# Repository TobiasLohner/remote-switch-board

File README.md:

# Remote Switch Board

This hardware project aims to provide a small form factor board for smart home projects.

The primary goal is to have a platform for remotely switching a garden watering system. The board can be partially populated if fewer switching outputs or other features are not required.

The board was made with KiCad 6.0.

## Main Features

* 8 solid state switches with current measurement
* SX1231 RF chip (compatible to RFM69, 433 / 868 / 915 MHz ISM frequency bands)
* STM32L0 microcontroller (optional)
* Raspberry PI header (optional)
* Frequency counter input
* Thermistor input
* Operating voltage: 12 V DC

## Microcontroller

The board has the option to either use an STM32L0 microcontroller or a Raspberry Pi to control the RF module and the switches. The microcontroller uses SPI to:
* control the switches via a shift register
* read the current feedback from a MCP3008
* communicate with the SX1231 RF chip

Further digital/analog inputs are used for:
* Thermistor input (analog input)
* Frequency counter (digital input)

Both SPI and digital input is also wired to the Raspberry PI header, such that a Raspberry Pi could be used instead of the microcontroller.

## SX1231
The SX1231 is a RF tranciever capable to be operated at license-free 433 / 868 / 915 MHz frequency bands. Tested range using 868 MHz was more than 500 meter in line-of-sight, sufficient for smart home applications.

## Electrical Characteristics
* Main operating voltage: 12 V
* Includes 5 V output to supply a Raspberry PI
* Total current limit approx. 5 A (might be more, untested)
* Switches: 12 V / 2.5 A each

# Licence
Shield: [![CC BY-SA 4.0][cc-by-sa-shield]][cc-by-sa]

This work is licensed under a
[Creative Commons Attribution-ShareAlike 4.0 International License][cc-by-sa].

[![CC BY-SA 4.0][cc-by-sa-image]][cc-by-sa]

[cc-by-sa]: http://creativecommons.org/licenses/by-sa/4.0/
[cc-by-sa-image]: https://licensebuttons.net/l/by-sa/4.0/88x31.png
[cc-by-sa-shield]: https://img.shields.io/badge/License-CC%20BY--SA%204.0-lightgrey.svg

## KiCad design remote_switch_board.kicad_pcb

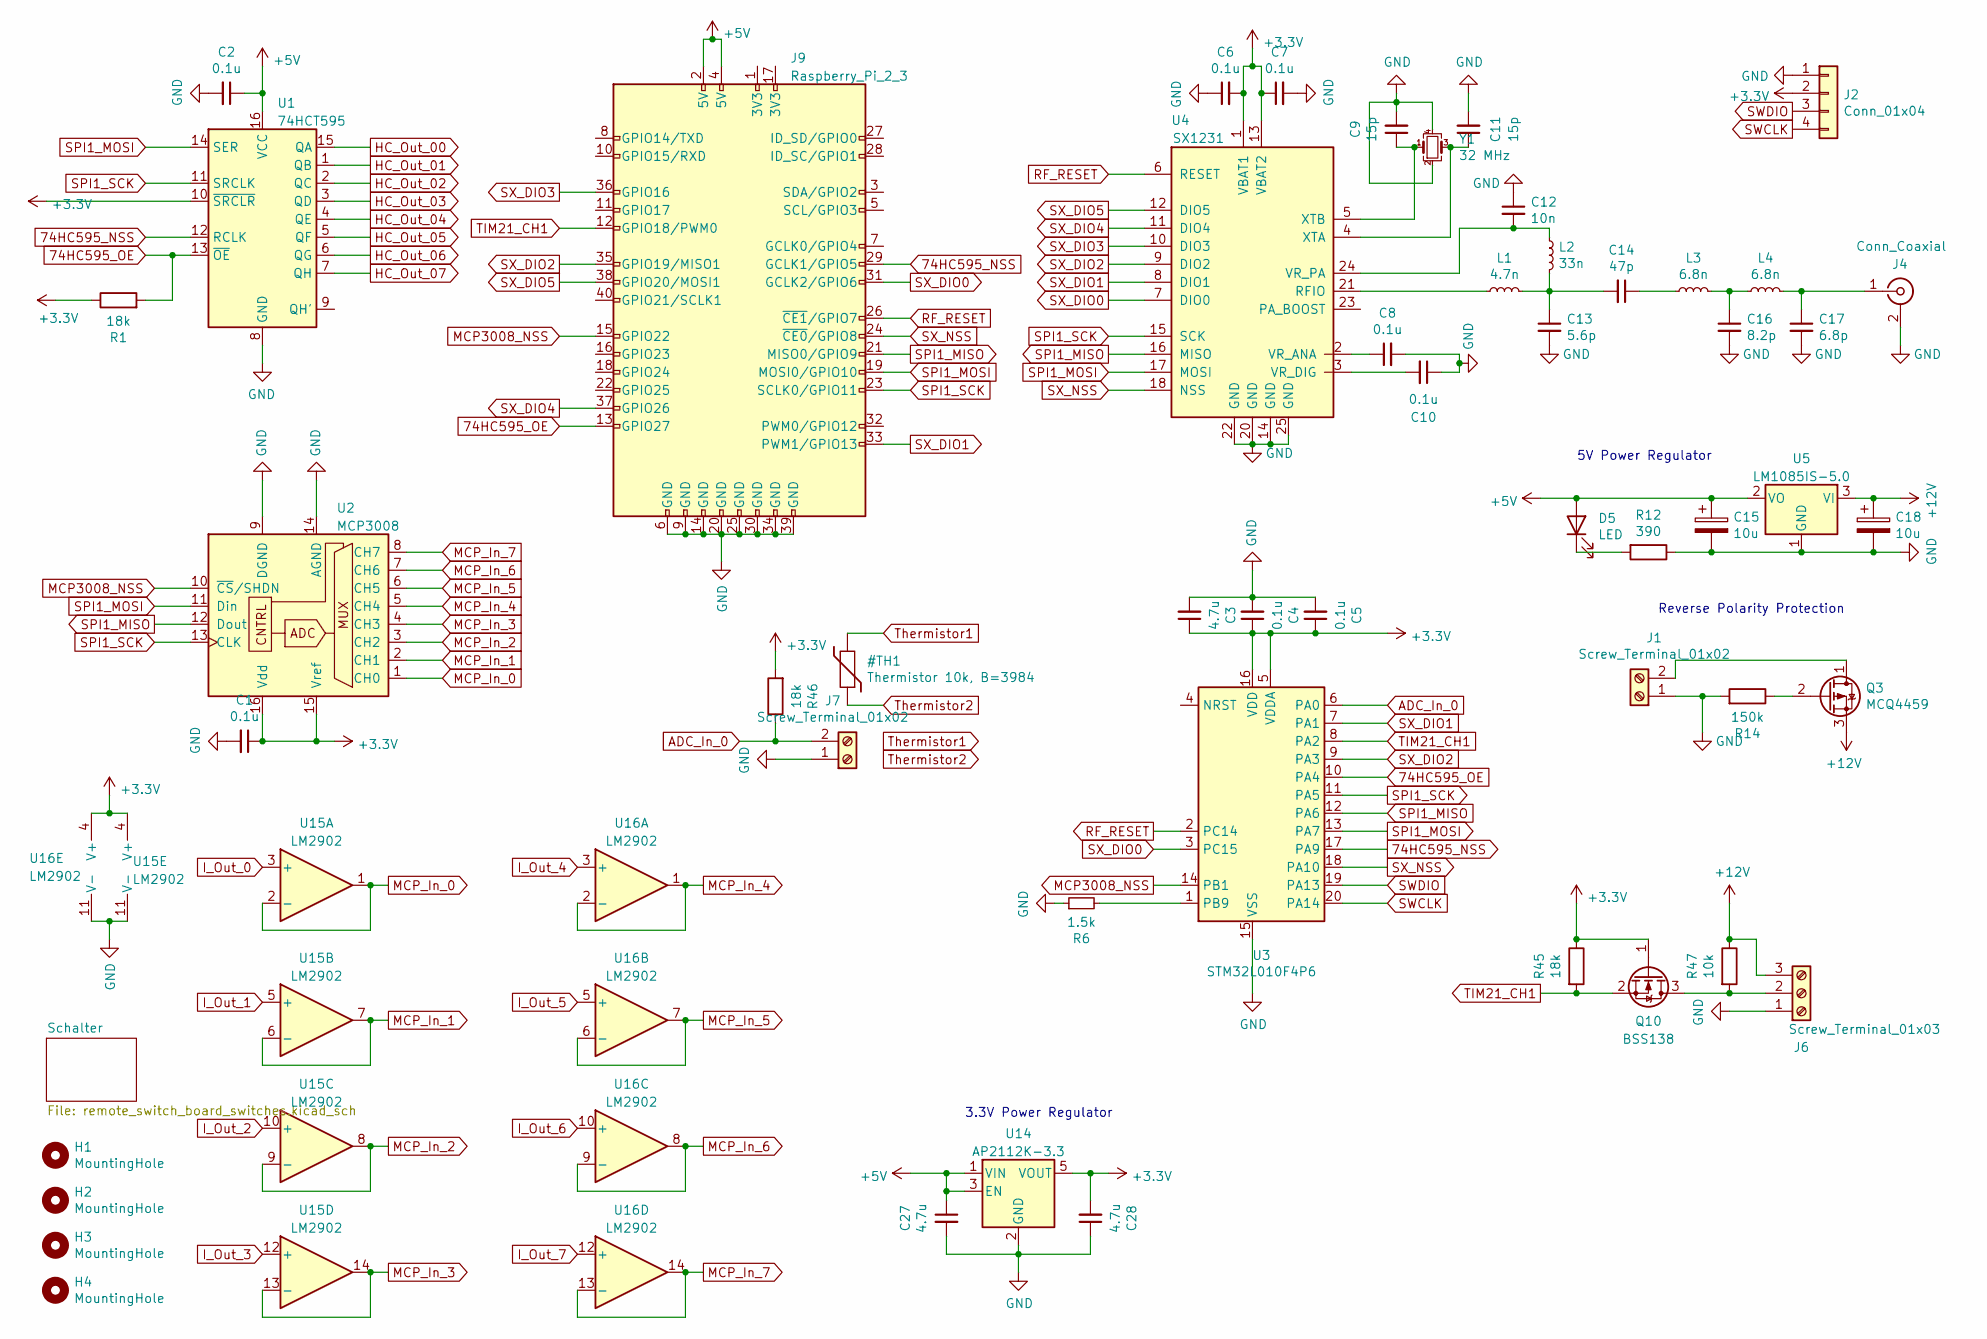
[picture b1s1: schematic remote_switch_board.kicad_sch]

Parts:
C1, C2, C4, C5, C6, C7, C8, C10: 0.1u; C_0603_1608Metric; Mouser-Nr. 581-0603YC104MAT4A
C3, C27, C28: 4.7u; C_0603_1608Metric; Mouser-Nr. 187-CL10B475KQ8NQNC
C9, C11: 15p; C_0603_1608Metric; Mouser-Nr. 80-C0603C150J5G
C12: 10n; C_0603_1608Metric; Mouser-Nr. 581-06035C103MAT4A
C13: 5.6p; C_0603_1608Metric; Mouser-Nr. 581-06035A5R6J
C14: 47p; C_0603_1608Metric; Mouser-Nr. 80-C0603C470J1G
C15, C18: 10u; CP_EIA-7343-31_Kemet-D; Mouser-Nr. 74-TR3D106K035C0400
C16: 8.2p; C_0603_1608Metric; Mouser-Nr. 80-C0603C829J5G
C17: 6.8p; C_0603_1608Metric; Mouser-Nr. 80-C0603C689J5G
D5: LED; LED_0805_2012Metric
H1, H2, H3, H4: MountingHole; MountingHole_2.7mm_Pad
J1, J7: Screw_Terminal_01x02; TerminalBlock_Phoenix_PT-1,5-2-3.5-H_1x02_P3.50mm_Horizontal; Mouser-Nr. 651-1984617
J2: Conn_01x04; PinHeader_1x04_P2.54mm_Vertical
J4: Conn_Coaxial; U.FL_Hirose_U.FL-R-SMT-1_Vertical; Mouser-Nr. 798-U.FL-R-SMT-110
J6: Screw_Terminal_01x03; TerminalBlock_Phoenix_PT-1,5-3-3.5-H_1x03_P3.50mm_Horizontal; Mouser-Nr. 651-1984620
J9: Raspberry_Pi_2_3; PinHeader_2x20_P2.54mm_Vertical
L1: 4.7n; L_0603_1608Metric; Mouser-Nr. 81-LQW18AN4N7C80D
L2: 33n; L_0603_1608Metric; Mouser-Nr. 81-LQW18AN33NJ00D
L3, L4: 6.8n; L_0603_1608Metric; Mouser-Nr. 81-LQW18AN6N8C00D
Q3: MCQ4459; MCQ4459_SOP-8_5.28x5.23mm_P1.27mm; Mouser-Nr. 833-MCQ4459-TP
Q10: BSS138; SOT-23; Mouser-Nr. 771-BSS138P215
R1, R45, R46: 18k; R_0603_1608Metric; Mouser-Nr. 603-RC0603FR-1018KL
R6: 1.5k; R_0603_1608Metric; Mouser-Nr. 652-CR0603FX-1501ELF
R12: 390; R_0603_1608Metric; Mouser-Nr. 603-RC0603FR-07390RL
R14: 150k; R_0603_1608Metric; Mouser-Nr. 603-RC0603FR-07150KL
R47: 10k; R_0603_1608Metric; Mouser-Nr. 603-RC0603FR-1010KL
U1: 74HCT595; TSSOP-16_4.4x5mm_P0.65mm; Mouser-Nr. 74HCT595PW,118
U2: MCP3008; SOIC-16_3.9x9.9mm_P1.27mm; Mouser-Nr. 579-MCP3008T-I/SL
U3: STM32L010F4P6; TSSOP-20_4.4x6.5mm_P0.65mm; Mouser-Nr. 511-STM32L010F4P6
U4: SX1231; QFN-24-1EP_5x5mm_P0.65mm_EP3.4x3.4mm; Mouser-Nr. 947-SX1231IMLTRT
U5: LM1085IS-5.0; TO-263-3_TabPin2; Mouser-Nr. 926-LM1085IS50NOPB
U14: AP2112K-3.3; SOT-23-5
U15, U16: LM2902; TSSOP-14_4.4x5mm_P0.65mm
Y1: 32 MHz; Crystal_SMD_2520-4Pin_2.5x2.0mm; Mouser-Nr. 344-NX2520SA32MCSW2

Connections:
74HC595_NSS: J9.29 (GCLK1/GPIO5), U1.12 (RCLK), U3.17 (PA9)
74HC595_OE: J9.13 (GPIO27), R1.2, U1.13 (~OE), U3.10 (PA4)
+3.3V: C1.1, C3.1, C4.1, C5.1, C6.2, C7.1, C28.2, J2.2, Q10.1 (G), R1.1, R45.1, R46.2, U1.10 (~SRCLR), U2.15 (Vref), U2.16 (Vdd), U3.5 (VDDA), U3.16 (VDD), U4.1 (VBAT1), U4.13 (VBAT2), U14.5 (VOUT), U15.4 (V+), U16.4 (V+); also elsewhere on the board
+5V: C2.1, C15.1, C27.1, D5.2 (A), J9.2 (5V), J9.4 (5V), U1.16 (VCC), U5.2 (VO), U14.1 (VIN), U14.3 (EN)
+12V: C18.1, J6.3, Q3.3 (S), R47.1, U5.3 (VI); also elsewhere on the board
ADC_In_0: J7.2, R46.1, U3.6 (PA0)
GND: C1.2, C2.2, C3.2, C4.2, C5.2, C6.1, C7.2, C8.2, C9.2, C10.1, C11.2, C12.1, C13.2, C15.2, C16.2, C17.2, C18.2, C27.2, C28.1, J1.1, J2.1, J4.2 (Ext), J6.1, J7.1, J9.6 (GND), J9.9 (GND), J9.14 (GND), J9.20 (GND), J9.25 (GND), J9.30 (GND), J9.34 (GND), J9.39 (GND), R6.1, R12.1, R14.2, U1.8 (GND), U2.9 (DGND), U2.14 (AGND), U3.15 (VSS), U4.14 (GND), U4.20 (GND), U4.22 (GND), U4.25 (GND), U5.1 (GND), U14.2 (GND), U15.11 (V-), U16.11 (V-), Y1.2, Y1.4; also elsewhere on the board
HC_Out_00: U1.15 (QA); also elsewhere on the board
HC_Out_01: U1.1 (QB); also elsewhere on the board
HC_Out_02: U1.2 (QC); also elsewhere on the board
HC_Out_03: U1.3 (QD); also elsewhere on the board
HC_Out_04: U1.4 (QE); also elsewhere on the board
HC_Out_05: U1.5 (QF); also elsewhere on the board
HC_Out_06: U1.6 (QG); also elsewhere on the board
HC_Out_07: U1.7 (QH); also elsewhere on the board
I_Out_0: U15.3 (+); also elsewhere on the board
I_Out_1: U15.5 (+); also elsewhere on the board
I_Out_2: U15.10 (+); also elsewhere on the board
I_Out_3: U15.12 (+); also elsewhere on the board
I_Out_4: U16.3 (+); also elsewhere on the board
I_Out_5: U16.5 (+); also elsewhere on the board
I_Out_6: U16.10 (+); also elsewhere on the board
I_Out_7: U16.12 (+); also elsewhere on the board
MCP3008_NSS: J9.15 (GPIO22), U2.10 (~CS/SHDN), U3.14 (PB1)
MCP_In_0: U2.1 (CH0), U15.1, U15.2 (-)
MCP_In_1: U2.2 (CH1), U15.6 (-), U15.7
MCP_In_2: U2.3 (CH2), U15.8, U15.9 (-)
MCP_In_3: U2.4 (CH3), U15.13 (-), U15.14
MCP_In_4: U2.5 (CH4), U16.1, U16.2 (-)
MCP_In_5: U2.6 (CH5), U16.6 (-), U16.7
MCP_In_6: U2.7 (CH6), U16.8, U16.9 (-)
MCP_In_7: U2.8 (CH7), U16.13 (-), U16.14
unnamed: C8.1, U4.2 (VR_ANA)
unnamed: C9.1, U4.5 (XTB), Y1.1
unnamed: C10.2, U4.3 (VR_DIG)
unnamed: C11.1, U4.4 (XTA), Y1.3
unnamed: C12.2, L2.1, U4.24 (VR_PA)
unnamed: C13.1, C14.2, L1.2, L2.2
unnamed: C14.1, L3.1
unnamed: C16.1, L3.2, L4.1
unnamed: C17.1, J4.1 (In), L4.2
unnamed: D5.1 (K), R12.2
unnamed: J1.2, Q3.1 (D)
unnamed: J6.2, Q10.3 (D), R47.2
unnamed: L1.1, U4.21 (RFIO)
unnamed: Q3.2 (G), R14.1
unnamed: R6.2, U3.1 (PB9)
RF_RESET: J9.26 (~CE1/GPIO7), U3.2 (PC14), U4.6 (RESET)
SPI1_MISO: J9.21 (MISO0/GPIO9), U2.12 (Dout), U3.12 (PA6), U4.16 (MISO)
SPI1_MOSI: J9.19 (MOSI0/GPIO10), U1.14 (SER), U2.11 (Din), U3.13 (PA7), U4.17 (MOSI)
SPI1_SCK: J9.23 (SCLK0/GPIO11), U1.11 (SRCLK), U2.13 (CLK), U3.11 (PA5), U4.15 (SCK)
SWCLK: J2.4, U3.20 (PA14)
SWDIO: J2.3, U3.19 (PA13)
SX_DIO0: J9.31 (GCLK2/GPIO6), U3.3 (PC15), U4.7 (DIO0)
SX_DIO1: J9.33 (PWM1/GPIO13), U3.7 (PA1), U4.8 (DIO1)
SX_DIO2: J9.35 (GPIO19/MISO1), U3.9 (PA3), U4.9 (DIO2)
SX_DIO3: J9.36 (GPIO16), U4.10 (DIO3)
SX_DIO4: J9.37 (GPIO26), U4.11 (DIO4)
SX_DIO5: J9.38 (GPIO20/MOSI1), U4.12 (DIO5)
SX_NSS: J9.24 (~CE0/GPIO8), U3.18 (PA10), U4.18 (NSS)
TIM21_CH1: J9.12 (GPIO18/PWM0), Q10.2 (S), R45.2, U3.8 (PA2)

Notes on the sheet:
3.3V Power Regulator
Reverse Polarity Protection
5V Power Regulator

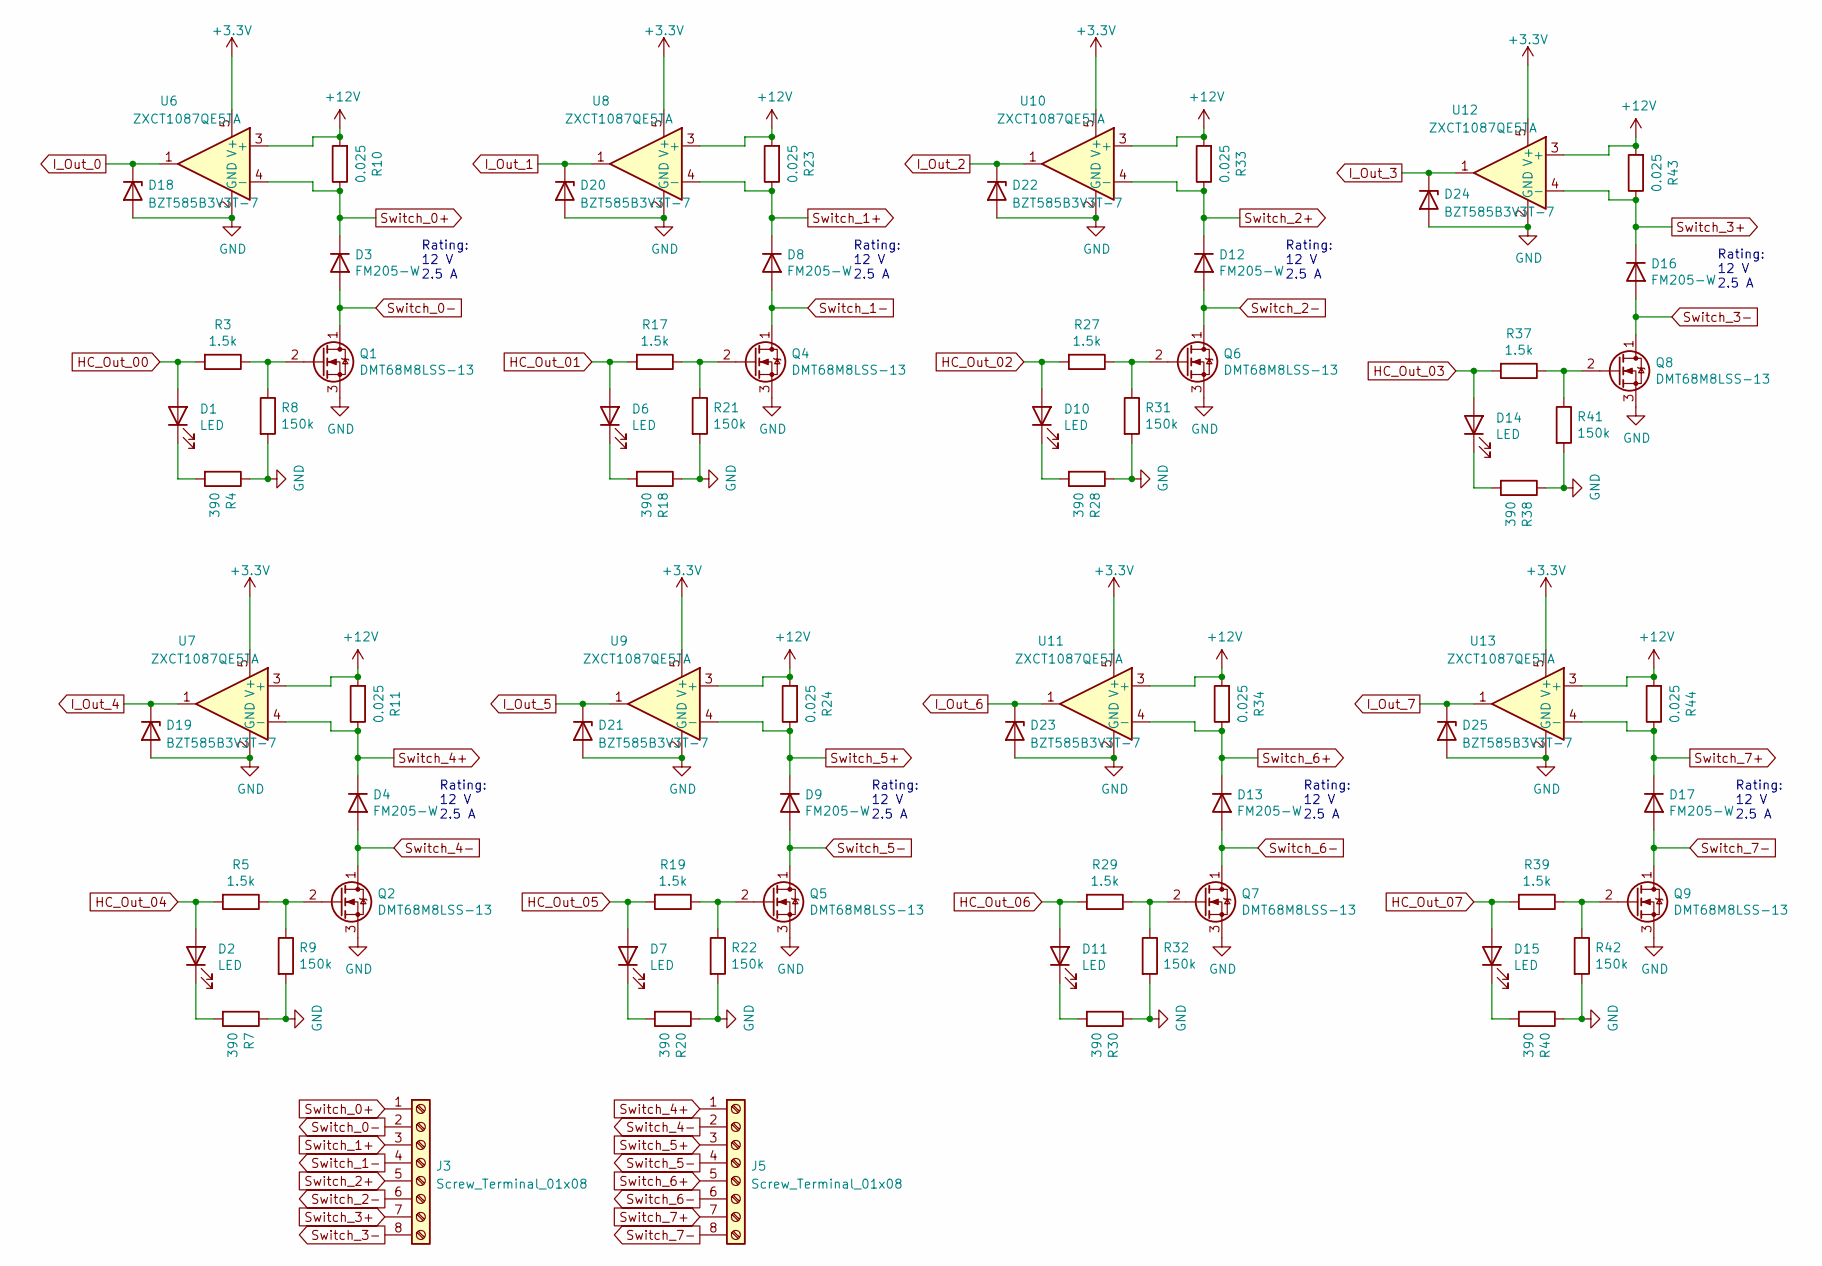
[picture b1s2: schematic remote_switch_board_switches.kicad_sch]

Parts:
D1, D2, D6, D7, D10, D11, D14, D15: LED; LED_0805_2012Metric
D3, D4, D8, D9, D12, D13, D16, D17: FM205-W; D_SMB; Mouser-Nr. 583-FM205
D18, D19, D20, D21, D22, D23, D24, D25: BZT585B3V3T-7; D_SOD-523; Mouser-Nr. 621-BZT585B3V3T-7
J3, J5: Screw_Terminal_01x08; TerminalBlock_Phoenix_PT-1,5-8-3.5-H_1x08_P3.50mm_Horizontal; Mouser-Nr. 651-1984675
Q1, Q2, Q4, Q5, Q6, Q7, Q8, Q9: DMT68M8LSS-13; DMT68M8LSS-13_SO-8_5.3x6.2mm_P1.27mm; Mouser-Nr. 621-DMT68M8LSS-13
R3, R5, R17, R19, R27, R29, R37, R39: 1.5k; R_0603_1608Metric; Mouser-Nr. 652-CR0603FX-1501ELF
R4, R7, R18, R20, R28, R30, R38, R40: 390; R_0603_1608Metric; Mouser-Nr. 603-RC0603FR-07390RL
R8, R9, R21, R22, R31, R32, R41, R42: 150k; R_0603_1608Metric; Mouser-Nr. 603-RC0603FR-07150KL
R10, R11, R23, R24, R33, R34, R43, R44: 0.025; R_1206_3216Metric; Mouser-Nr. 708-CSR1206FK25L0
U6, U7, U8, U9, U10, U11, U12, U13: ZXCT1087QE5TA; SOT-23-5; Mouser-Nr. 621-ZXCT1087QE5TA

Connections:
+3.3V: U6.5 (V+), U7.5 (V+), U8.5 (V+), U9.5 (V+), U10.5 (V+), U11.5 (V+), U12.5 (V+), U13.5 (V+); also elsewhere on the board
+12V: R10.2, R11.2, R23.2, R24.2, R33.2, R34.2, R43.2, R44.2, U6.3 (+), U7.3 (+), U8.3 (+), U9.3 (+), U10.3 (+), U11.3 (+), U12.3 (+), U13.3 (+); also elsewhere on the board
GND: D18.2 (A), D19.2 (A), D20.2 (A), D21.2 (A), D22.2 (A), D23.2 (A), D24.2 (A), D25.2 (A), Q1.3 (S), Q2.3 (S), Q4.3 (S), Q5.3 (S), Q6.3 (S), Q7.3 (S), Q8.3 (S), Q9.3 (S), R4.1, R7.1, R8.2, R9.2, R18.1, R20.1, R21.2, R22.2, R28.1, R30.1, R31.2, R32.2, R38.1, R40.1, R41.2, R42.2, U6.2 (GND), U7.2 (GND), U8.2 (GND), U9.2 (GND), U10.2 (GND), U11.2 (GND), U12.2 (GND), U13.2 (GND); also elsewhere on the board
HC_Out_00: D1.2 (A), R3.2; also elsewhere on the board
HC_Out_01: D6.2 (A), R17.2; also elsewhere on the board
HC_Out_02: D10.2 (A), R27.2; also elsewhere on the board
HC_Out_03: D14.2 (A), R37.2; also elsewhere on the board
HC_Out_04: D2.2 (A), R5.2; also elsewhere on the board
HC_Out_05: D7.2 (A), R19.2; also elsewhere on the board
HC_Out_06: D11.2 (A), R29.2; also elsewhere on the board
HC_Out_07: D15.2 (A), R39.2; also elsewhere on the board
I_Out_0: D18.1 (K), U6.1; also elsewhere on the board
I_Out_1: D20.1 (K), U8.1; also elsewhere on the board
I_Out_2: D22.1 (K), U10.1; also elsewhere on the board
I_Out_3: D24.1 (K), U12.1; also elsewhere on the board
I_Out_4: D19.1 (K), U7.1; also elsewhere on the board
I_Out_5: D21.1 (K), U9.1; also elsewhere on the board
I_Out_6: D23.1 (K), U11.1; also elsewhere on the board
I_Out_7: D25.1 (K), U13.1; also elsewhere on the board
unnamed: D1.1 (K), R4.2
unnamed: D2.1 (K), R7.2
unnamed: D6.1 (K), R18.2
unnamed: D7.1 (K), R20.2
unnamed: D10.1 (K), R28.2
unnamed: D11.1 (K), R30.2
unnamed: D14.1 (K), R38.2
unnamed: D15.1 (K), R40.2
unnamed: Q1.2 (G), R3.1, R8.1
unnamed: Q2.2 (G), R5.1, R9.1
unnamed: Q4.2 (G), R17.1, R21.1
unnamed: Q5.2 (G), R19.1, R22.1
unnamed: Q6.2 (G), R27.1, R31.1
unnamed: Q7.2 (G), R29.1, R32.1
unnamed: Q8.2 (G), R37.1, R41.1
unnamed: Q9.2 (G), R39.1, R42.1
Switch_0+: D3.1 (K), J3.1, R10.1, U6.4 (-)
Switch_0-: D3.2 (A), J3.2, Q1.1 (D)
Switch_1+: D8.1 (K), J3.3, R23.1, U8.4 (-)
Switch_1-: D8.2 (A), J3.4, Q4.1 (D)
Switch_2+: D12.1 (K), J3.5, R33.1, U10.4 (-)
Switch_2-: D12.2 (A), J3.6, Q6.1 (D)
Switch_3+: D16.1 (K), J3.7, R43.1, U12.4 (-)
Switch_3-: D16.2 (A), J3.8, Q8.1 (D)
Switch_4+: D4.1 (K), J5.1, R11.1, U7.4 (-)
Switch_4-: D4.2 (A), J5.2, Q2.1 (D)
Switch_5+: D9.1 (K), J5.3, R24.1, U9.4 (-)
Switch_5-: D9.2 (A), J5.4, Q5.1 (D)
Switch_6+: D13.1 (K), J5.5, R34.1, U11.4 (-)
Switch_6-: D13.2 (A), J5.6, Q7.1 (D)
Switch_7+: D17.1 (K), J5.7, R44.1, U13.4 (-)
Switch_7-: D17.2 (A), J5.8, Q9.1 (D)

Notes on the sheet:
Rating: 12 V 2.5 A

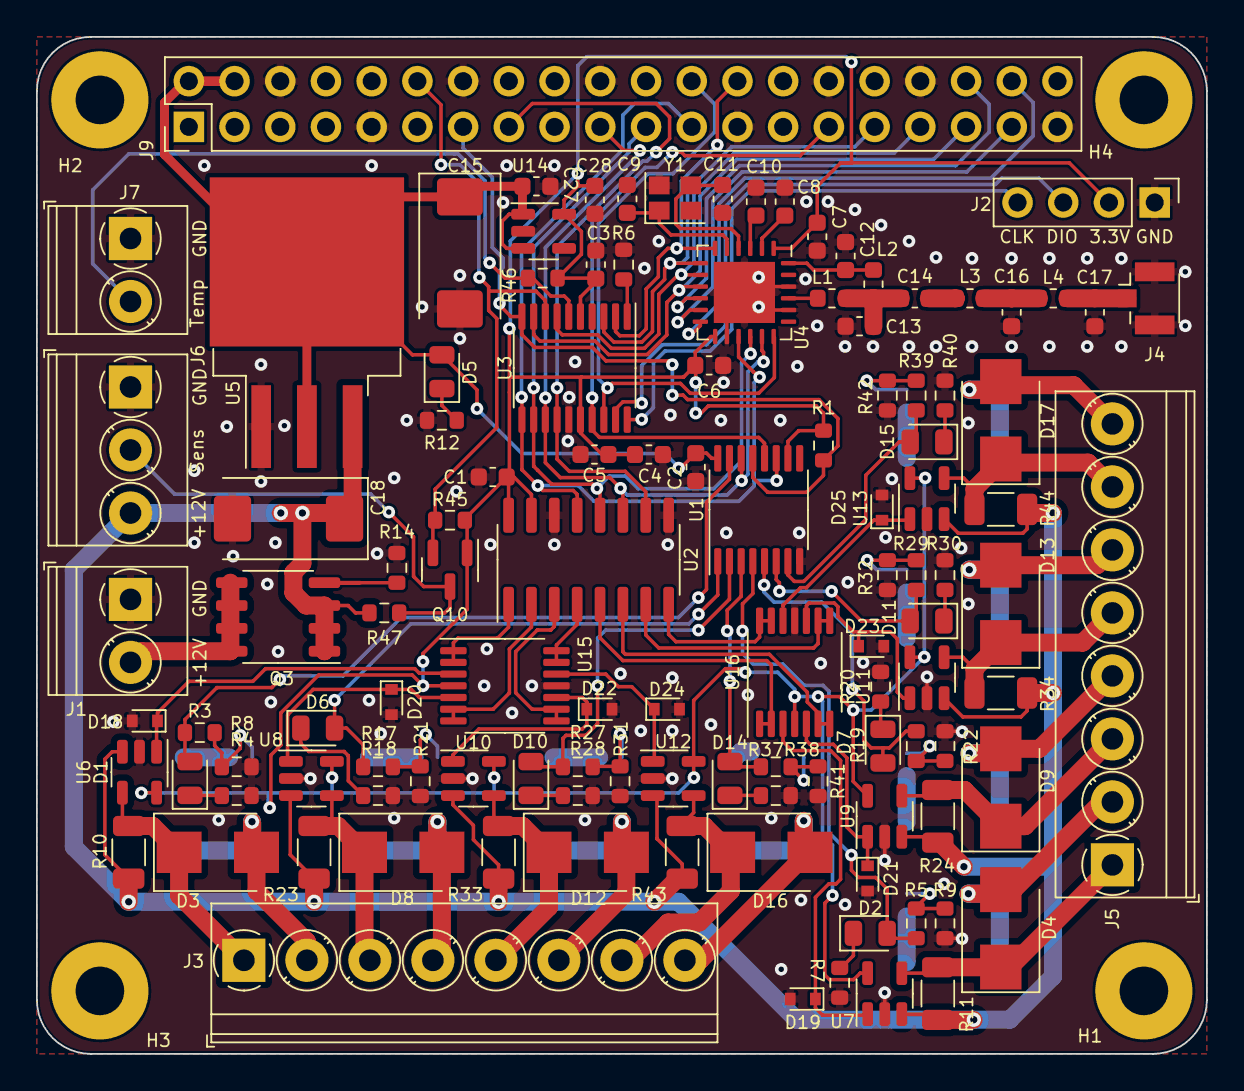
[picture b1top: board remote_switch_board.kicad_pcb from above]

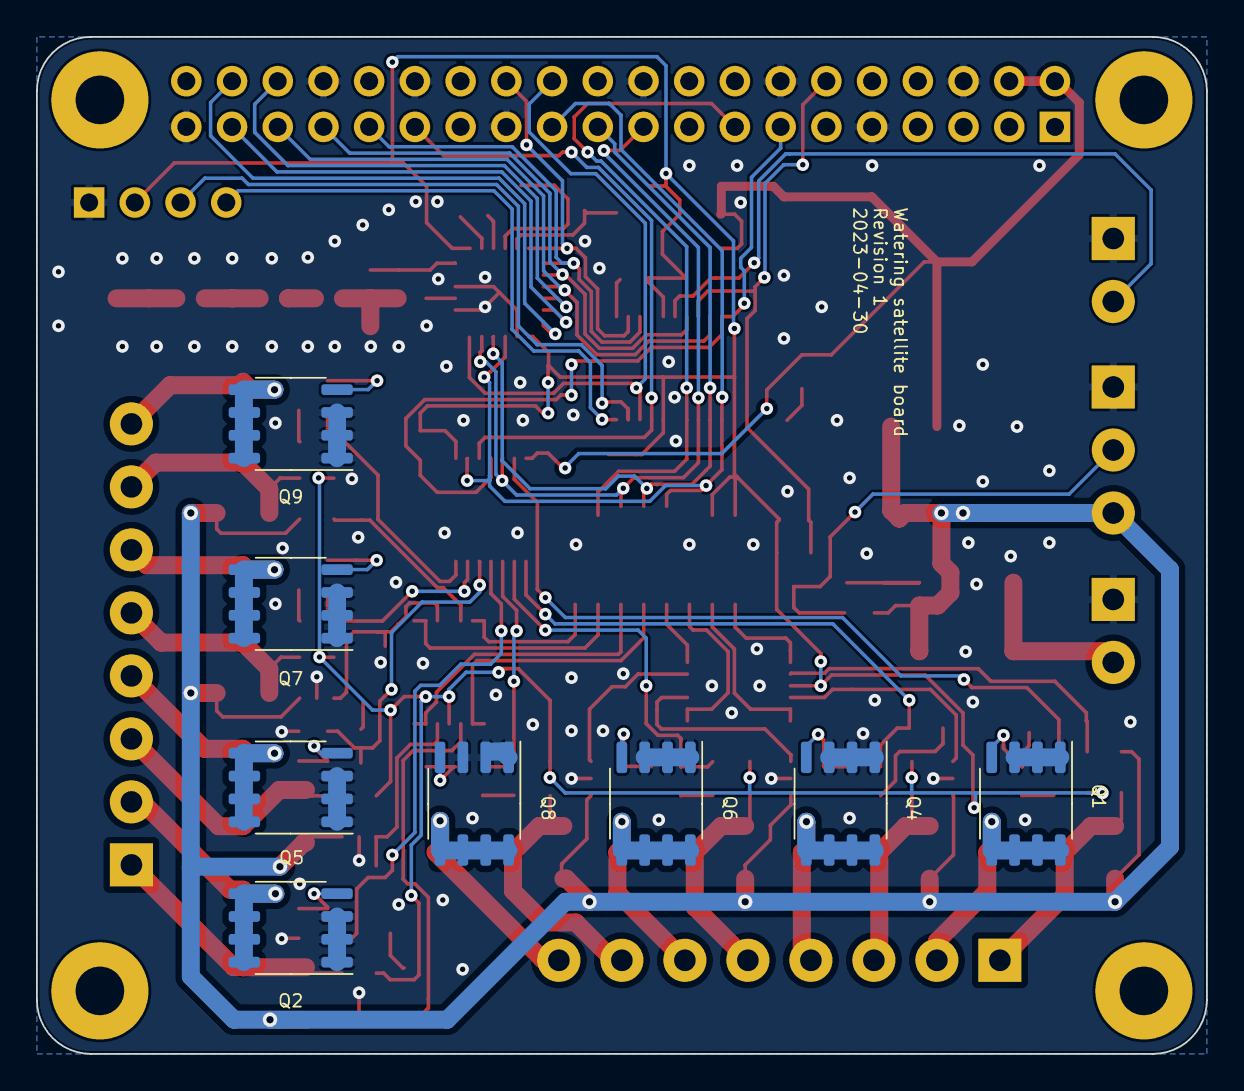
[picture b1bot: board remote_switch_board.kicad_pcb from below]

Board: 2 copper layers, 65.0 x 56.5 mm, 127 parts (8 on the bottom side), 93 nets.

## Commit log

2023-07-27 Initial import
